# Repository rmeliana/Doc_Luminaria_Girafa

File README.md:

Tutorial Projeto Luminária Girafa

* O que é o Projeto Luminária Girafa?

  O projeto Luminária Girafa foi criado com objetivo de ingressar novos usuários à área de fabricação digital na disciplina de Natureza do Design no Insper. Baseado no [trabalho final](http://archive.fabacademy.org/archives/2017/fablabinsper/students/5/project02.html) do curso de Fab Academy do professor Victor Macul, e adaptado com auxílio da Equipe Técnica do Fab Lab Insper. Trata-se de uma luminária em formato de girafa, com corpo e cabeça em chapas de MDF, bulbos em impressão 3D e circuito eletrônico para a iluminação.

* Como fazer o download dos arquivos?

  Para utilizar os arquivos deste repositório realize o download completo de todos os arquivos na [tela principal](https://github.com/rmeliana/Doc_Luminaria_Girafa). Clique no botão **Code** para expandir o menu, em seguida clique em **Download ZIP**.
  No arquivo "TUTORIAL LUMINÁRIA GIRAFA.pdf" consta o passo a passo do desenvolvimento, assim como os materiais e ferramentas necessárias. Os hiperlinks nesse documento funcionam apenas no arquivo pdf baixado.

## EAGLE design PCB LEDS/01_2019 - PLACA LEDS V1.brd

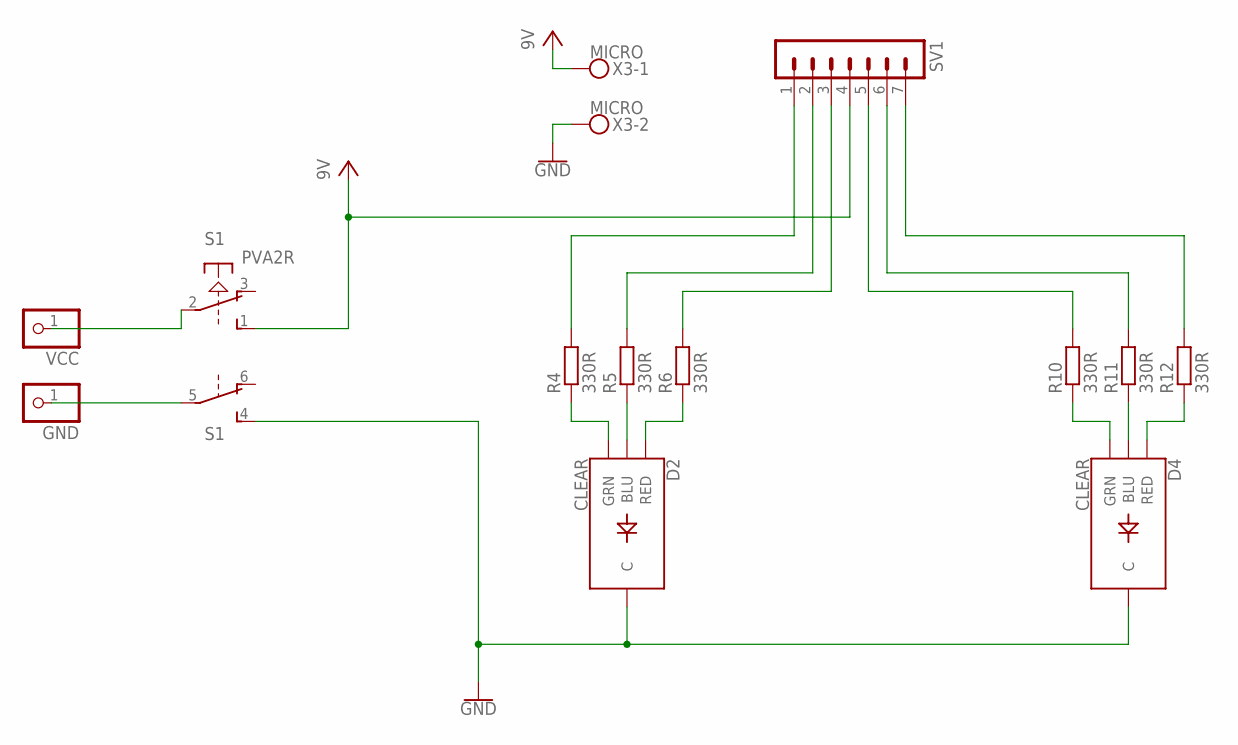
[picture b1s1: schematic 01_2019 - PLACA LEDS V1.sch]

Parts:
D2, D4: CLEAR; LED-RGB-THRU
GND: PINHD-1X1; 1X01
R4, R5, R6, R10, R11, R12: 330R; 0204/7
S1: PVA2R
SV1: MA07-1
VCC: PINHD-1X1; 1X01
X3: MICRO; MKDSN1,5/2-5,08

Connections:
GND: D2.2 (C), D4.2 (C), S1.4 (S), X3.2
unnamed: R12.2, SV1.7
unnamed: S1.2, VCC.1
unnamed: D2.3 (GRN), R4.1
unnamed: D2.4 (BLU), R5.1
unnamed: D2.1 (RED), R6.1
unnamed: GND.1, S1.5
unnamed: R6.2, SV1.3
unnamed: R5.2, SV1.2
unnamed: R4.2, SV1.1
unnamed: D4.3 (GRN), R10.1
unnamed: D4.4 (BLU), R11.1
unnamed: D4.1 (RED), R12.1
unnamed: R10.2, SV1.5
unnamed: R11.2, SV1.6
VCC: S1.1 (S), SV1.4, X3.1

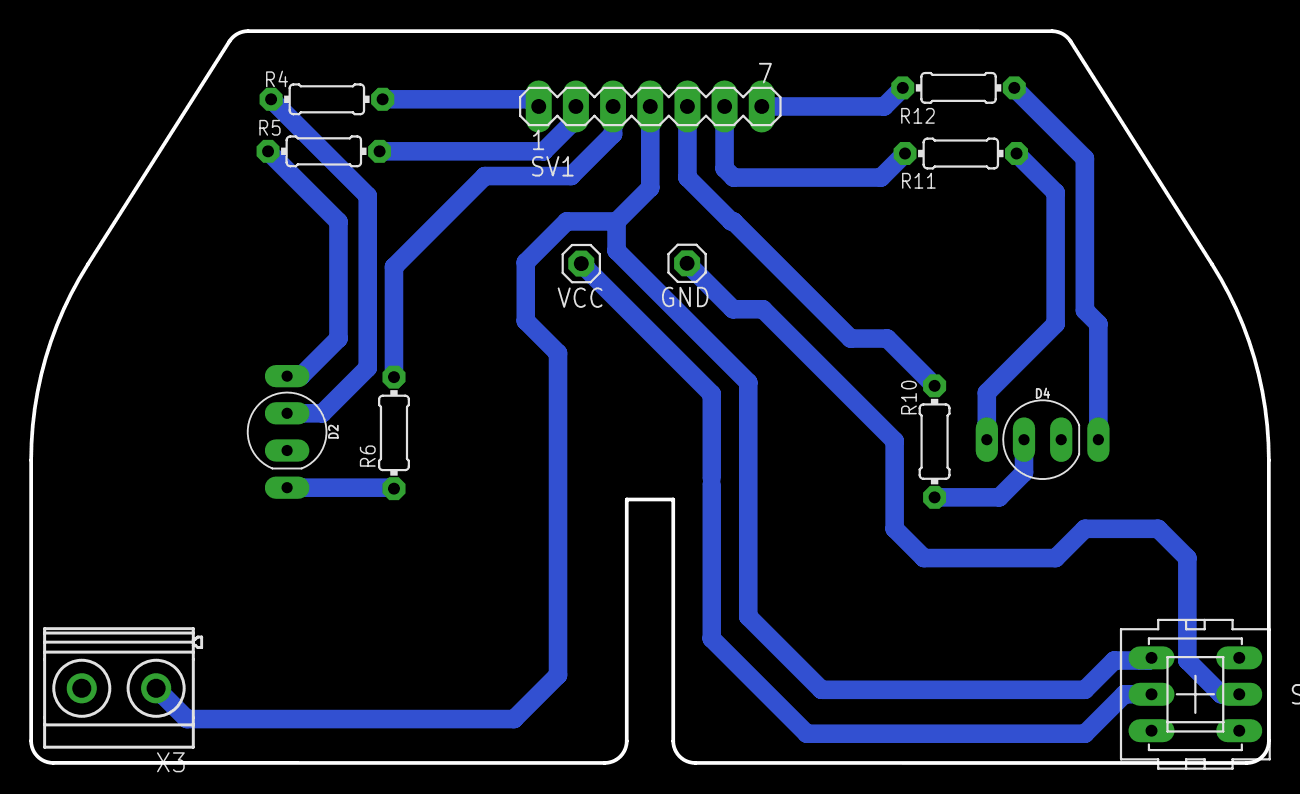
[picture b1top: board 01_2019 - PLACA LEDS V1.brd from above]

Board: 2 copper layers, 84.6 x 50.0 mm, 13 parts (0 on the bottom side), 16 nets.

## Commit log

2021-04-29 Update README.md
    Inserindo descrição.
2021-05-06 Modelo 3D da montagem completa da Luminária Girafa
2021-05-06 Arquivos da Placa Eletrônica da Luminária Girafa
2021-05-06 Arquivos do Bulbo da Luminária Girafa
2021-05-06 Arquivos de furação
2021-05-06 Projeto FlatCAM da placa eletrônica
2021-05-06 Arquivos DXF peças cabeça da Luminária Girafa
2021-05-06 Arquivos DXF das peças da cabeça Luminária Girafa
2021-05-06 Arquivos para corte dos óculos da Luminária Girafa
2021-05-06 Arquivos para usinagem do corpo
2021-05-07 Tutorial Luminária Girafa
2021-05-10 Tutorial de fabricação
    Links clicáveis ativos
2021-06-01 Layout PCB
2021-06-01 tips for electronic soldering
2021-06-04 dxf para router Elite
2021-06-07 revised file
2021-06-07 Versão final do Tutorial
2021-06-07 Versão final Tutorial Luminária Girafa
2021-06-08 Versão final 2
2021-06-08 Atualização
2021-06-28 Create LICENSE
2021-07-27 Informações sobre o projeto

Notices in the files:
parts and their libraries:
SparkFun-PowerSymbols: Licensing: Creative Commons ShareAlike 4.0 International - https://creativecommons.org/licenses/by-sa/4.0
